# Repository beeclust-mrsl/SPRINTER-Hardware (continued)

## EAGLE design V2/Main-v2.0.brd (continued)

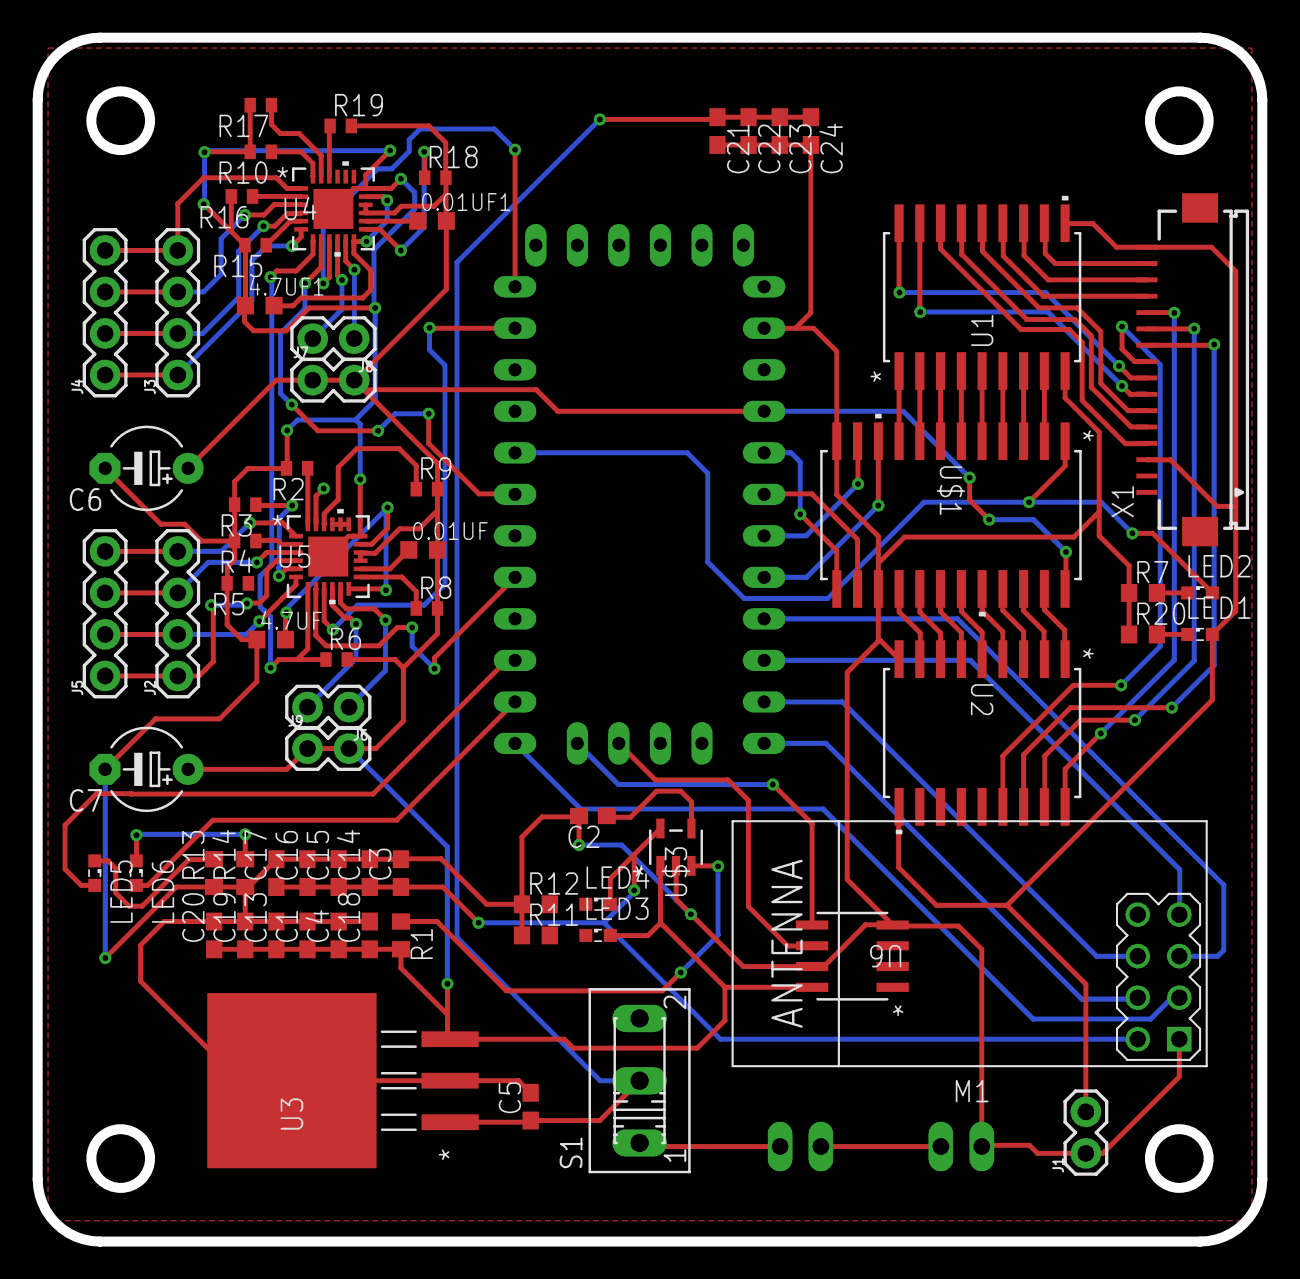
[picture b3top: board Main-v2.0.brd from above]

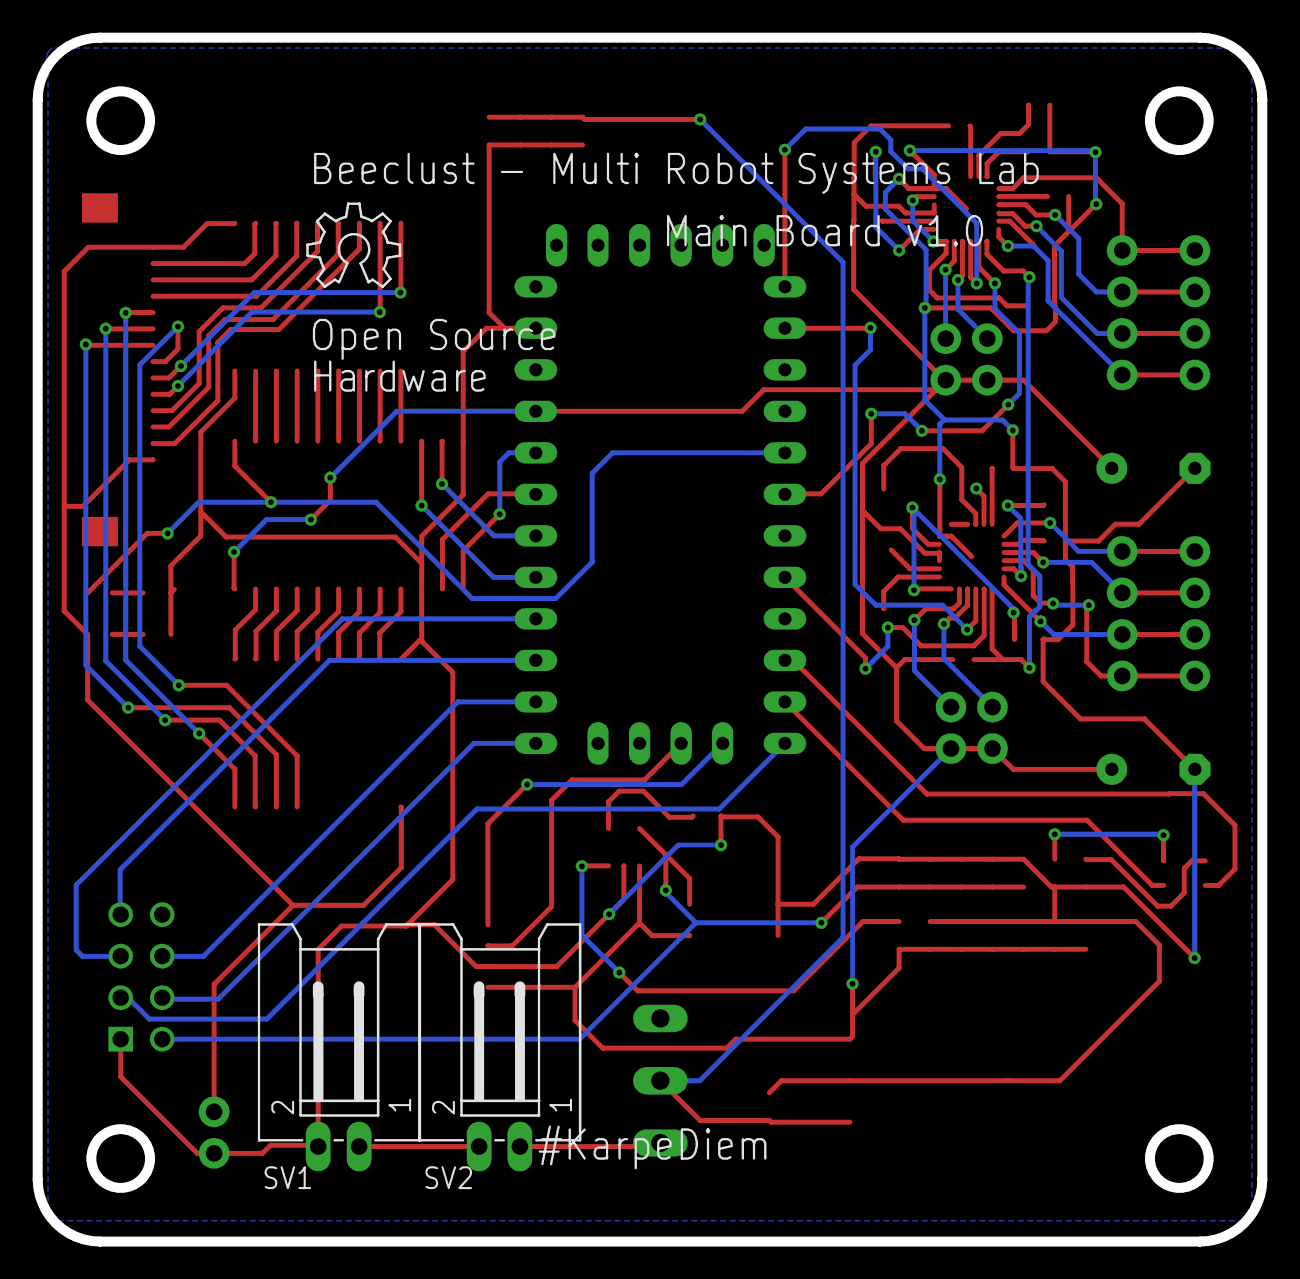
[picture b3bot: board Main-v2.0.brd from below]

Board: 2 copper layers, 74.9 x 73.7 mm, 74 parts (3 on the bottom side), 92 nets.

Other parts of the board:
U$4: OSHW_6X200_NOTEXT

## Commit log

2020-01-18 V.5 Uploaded
2020-01-18 Added ULN Board Version
2020-01-19 Used SOIC package for Boost converter along with PTH Resistors
2020-01-20 Removed Redundant Files
2020-01-28 Added SPI connector for SD card and modified UART programmer to support ATmega in V5.1
2020-02-13 Updated silkscreen in V5.1 and voltage booster is replaced in V6.0
2020-02-14 Added space opti verion
2020-02-19 V6.0 Copy Routed Board
2020-02-21 Routing Cleanup V6.0
2020-02-23 V6.0 Updated
2020-02-23 Route airwires
